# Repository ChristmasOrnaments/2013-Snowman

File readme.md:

This is the first in a series of Christmas ornaments I started making in 2013.

***

I had been experimenting with the Attiny series of MCUs and the Arduino environment, so I decided to make it a little more interesting than just a bare PCB. Flashing lights! I searched google and found a lot more info than I thought I would, but they were all designed to be plugged into a wall outlet. It was clear that this would be more fun if it were an actual Christmas ornament hanging from the tree, and I hate dragging wires around the tree (especially for a single ornament).  So battery powered it must be.

Unfortunately, the number of LEDs I wanted to use (~12) would come out to a current drain of 240mA. That’s a lot for any battery, but especially a small battery. AAA batteries would probably work, but the low-voltage Attinys required at least 1.8V (1.6V works usually, but the LEDs wouldn’t work at that voltage anyway). Using 2 AAA batteries would probably cause the branches of most Christmas trees to bend so much the ornament would just fall off. I tried a few buck/boost converters (like the MCP1640) to see if I could run the ornament from a single AAA cell, but most of these are only about 85% efficiency (the best I ever got was 60%). The input power of the converter was fairly substantial (5-10mA idle). In addition, the boost converter would be operating constantly, so even if the LEDs weren't flashing, the battery would still have a 5-10mA draw on it. That's enough to drain a 1000mAh AAA battery in 4 days! I'm sure if I had spent more time trying to optimize the boost converter I could have made it work. The MCP1640 has an enable pin, so I could have used the MCU to put the converter to sleep, if I could find a charge pump that would work to wake the MCU, and then the converter. Too complicated...

I found an interesting technique for controlling many LEDs from only a few MCU pins, called [Charlieplexing](https://en.wikipedia.org/wiki/Charlieplexing)…  It’s a really simple concept, so if you haven't heard of it I suggest you read the wiki page. I did a little more research and found [the UnaClocker's blog](https://web.archive.org/web/20131228142659/http://www.neonsquirt.com/xmas_ornament2012.html), and he had already done what I was doing! Well, sort of. It was still wall-powered, but since charlieplexing never lights more than a single LED at once, the MAXIMUM current draw will be the MCU (which is a few milliamps, maybe) plus the current draw of a single LED. So, ~10mA. This could easily run from a 3V CR2032 watch battery. Small, lightweight, and available at every drug store!

I prototyped a  small panel of 12 charlieplexed LEDs and it worked great. I was able to control 12 separate LEDs from an Attiny85 (8-pin) MCU. The more LEDs you turn on at once, the dimmer they get (since it is multiplexing the LEDs and turning them on and off individually, very quickly).

Eventually I designed the PCB with the snowman on it, and etched a board for testing. You'll notice the PCB has a little pushbutton on it.  It's nothing fancy, it just resets the MCU which gives you the ability to "play" the light show whenever you want (the first thing the MCU does is run through the LED patterns, before going to sleep). Doing it this way also saves a pin in case I want  to add more LEDs to a future version.

Here's the schematic and some pics of the demo board:

I found that using a long list of *digitalWrite* commands to display a pattern wasn’t going to be very space efficient (these things max out at 8k, and I’d rather use the 4k version). I found [this instructable](https://www.instructables.com/CharliePlexed-LED-string-for-the-Arduino/) which uses a byte-array to store the patterns in the form of a single string of binary data representing a single "frame" of the pattern to display. It's just an array holding 1's and 0's.  

Matching each LED with the corresponding element of the array can be tricky, so I came up with an excel spreadsheet to help build the strings of bytes for each frame in the pattern. I used the *CONCATENATE* function to simply string the contents of all the cells into a single line separated by commas, just like in the array. I set the cells up with colored backgrounds so it looked like the LEDs on the PCB.  I also added a button macro to clear the cells out, so it would be a little easier to make each frame (I didn’t have to go reset each cell to 0, the button reset them all to 0 instantly). If you don't want to use the macro, simply build a new document using CONCATENATE (or whatever your office program provides).

That gave me a bunch of different patterns I could go through when lighting the LEDs. I found a nice little [battery run-time calculator](http://oregonembedded.com/batterycalc.htm) online, which helped me guess how long the batteries would last. It turns out, even at 10mA the CR2032 battery wouldn't last very long if it was running constantly.  Instead, it uses the hardware watchdog timer to wake the MCU every 8 seconds. It then increments a counter variable and goes back to sleep (it only draws a few microamps when sleeping). Once the counter reaches a certain value (SleepTime), it executes the functions to display LED patterns. 

Read through the code comments for an explanation of how that works, but basically you set SleepTime to however many seconds you want it to wait before it turns on again (so, 300=5 minutes, etc). Since I'm using the internal clocks of the MCUs (which are known to be very inaccurate) I also adjusted the times a little bit. if you want a 5 minute wake time, then you need to use something around 300, but 300 will almost certainly NOT be 5 minutes.

My first prototype lasted from the beginning of October through the following January. It really depends on the voltages of your LEDs. I liked blue and green (TRUE green) LEDs, which tend to have a forward voltage of 3V. that means the CR2032 battery (which is a 3V battery) has to be pretty full to get the LEDs to light up brightly.  They usually go out first, around 2.4V. The red and yellow LEDs actually continued to work for at least another month before I ended the test (the MCUs will work down to about 1.6V, below that they become unstable). I thought 5 months was plenty of battery life for something that was intended to last through December. That being said, I would avoid using blue since it starts to dim much quicker than the others.

I had the PCBs manufactured by iTead Studio and assembled them:

Here's the ornament in action:

### Compiling

* Install [ATTinyCore](https://github.com/spencekonde/attinycore) using the boards manager
* Select **Attiny25/45/85 (No bootloader)** from the boards list
* Set the *Clock source* to **4MHz (internal)** (With newer versions, you may need to use 8MHz with a scalar variable to lower it to 4MHz)
* Set *B.O.D* to **Disabled**
* Select **Burn Bootloader** to write the changes
* Compile and write the program to the MCU

If using another method to program the MCU, just remember you need to set the fuses properly both for correct speed and for the power saving features. The fuses (for an ATTINY45) should be:

Low: C3  
High: DF  
Extended: FF

You can see the effect of different fuse settings (and their values) [here](http://www.engbedded.com/fusecalc/).

### Resources

**Charlieplexing Code using a byte array:**  
[https://www.instructables.com/CharliePlexed-LED-string-for-the-Arduino/](https://www.instructables.com/CharliePlexed-LED-string-for-the-Arduino/)

**Battery calculator:**  
[http://oregonembedded.com/batterycalc.htm](http://oregonembedded.com/batterycalc.htm)

**Power saving information:**  
[http://www.gammon.com.au/forum/?id=11497](http://www.gammon.com.au/forum/?id=11497)  
[http://www.insidegadgets.com/2011/02/05/reduce-attiny-power-consumption-by-sleeping-with-the-watchdog-timer](http://www.insidegadgets.com/2011/02/05/reduce-attiny-power-consumption-by-sleeping-with-the-watchdog-timer/)  
[http://www.nongnu.org/avr-libc/user-manual/group\_\_avr\_\_power.html](http://www.nongnu.org/avr-libc/user-manual/group__avr__power.html)

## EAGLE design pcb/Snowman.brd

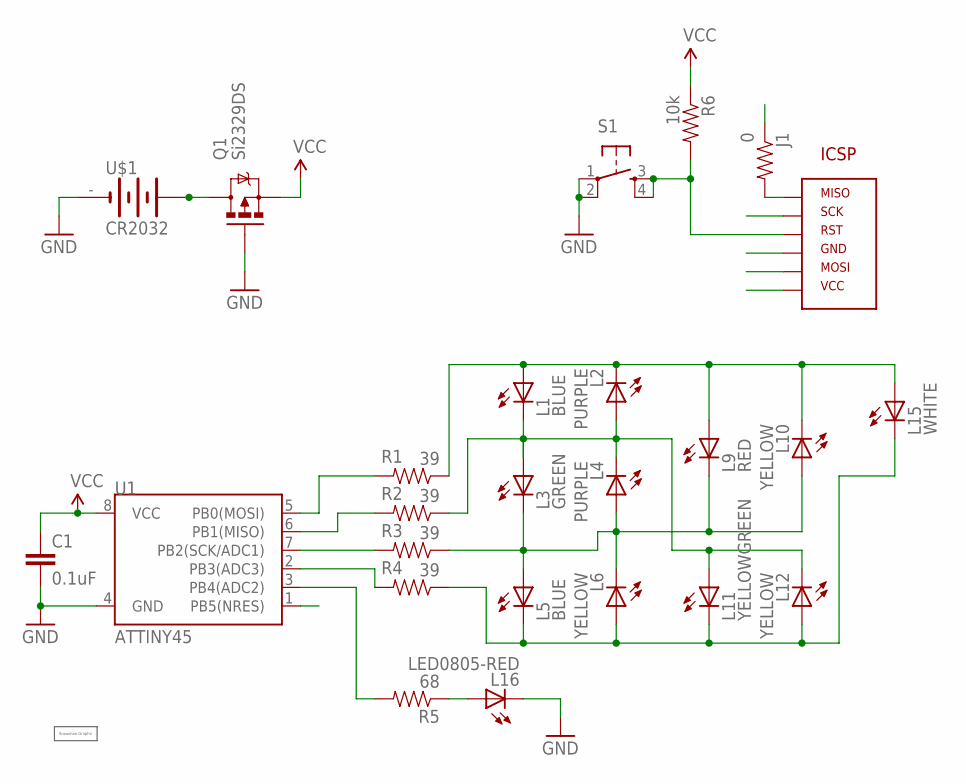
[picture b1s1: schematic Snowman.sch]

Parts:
C1: 0.1uF; 0805
J1: 0; 0805
L1, L5: BLUE; LED-0805-RED
L2, L4: PURPLE; LED-0805-GREEN
L3: GREEN; LED-0805-RED
L6, L10: YELLOW; LED-0805-GREEN
L9: RED; LED-0805-RED
L11: YELLOWGREEN; LED-0805-GREEN
L12: YELLOW; LED-0805-RED
L15: WHITE; LED-0805-RED
L16: LED0805-RED; LED-0805-RED
Q1: Si2329DS; SOT23-3
R1, R2, R3, R4: 39; 0805
R5: 68; 0805
R6: 10k; 0805
S1: TAC_SWITCHSMD; TACTILE_SWITCH_SMD
U1: ATTINY45; SO08-EIAJ
U$1: CR2032; BAT-HLD-001
U$2: 5X6_SNOWMAN5X5; 5X5_SNOWMAN
U$3: AVR_ICSP_6P6PIN; AVR_ICSP_6P_SMD

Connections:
GND: C1.2, L16.C, Q1.1 (G), S1.1, S1.2, U1.4 (GND), U$1.-, U$3.GND
L12: L1.C, L2.A, L3.A, L4.C, L11.A, L12.C, R2.1
MISO: J1.1, R2.2, U1.6 (PB1(MISO))
MOSI: R1.2, U1.5 (PB0(MOSI)), U$3.MOSI
unnamed: Q1.3 (D), U$1.+@1 (+), U$1.+@2 (+)
unnamed: R5.2, U1.3 (PB4(ADC2))
unnamed: L3.C, L4.A, L5.A, L6.C, L9.C, L10.A, R3.1
unnamed: R4.2, U1.2 (PB3(ADC3))
unnamed: L5.C, L6.A, L11.C, L12.A, L15.C, R4.1
unnamed: L1.A, L2.C, L9.A, L10.C, L15.A, R1.1
unnamed: L16.A, R5.1
unnamed: J1.2, U$3.MISO
RST: R6.2, S1.3, S1.4, U1.1 (PB5(NRES)), U$3.RST
SCK: R3.2, U1.7 (PB2(SCK/ADC1)), U$3.SCK
VCC: C1.1, Q1.2 (S), R6.1, U1.8 (VCC), U$3.VCC

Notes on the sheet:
ICSP

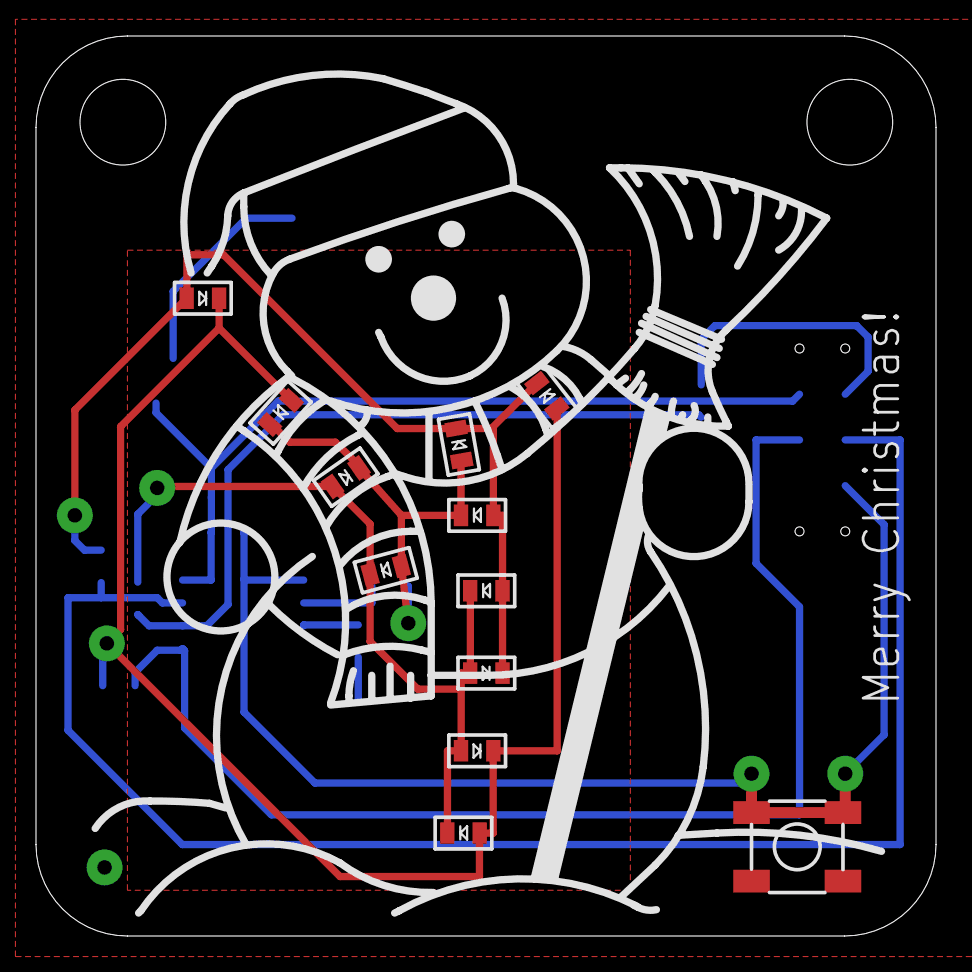
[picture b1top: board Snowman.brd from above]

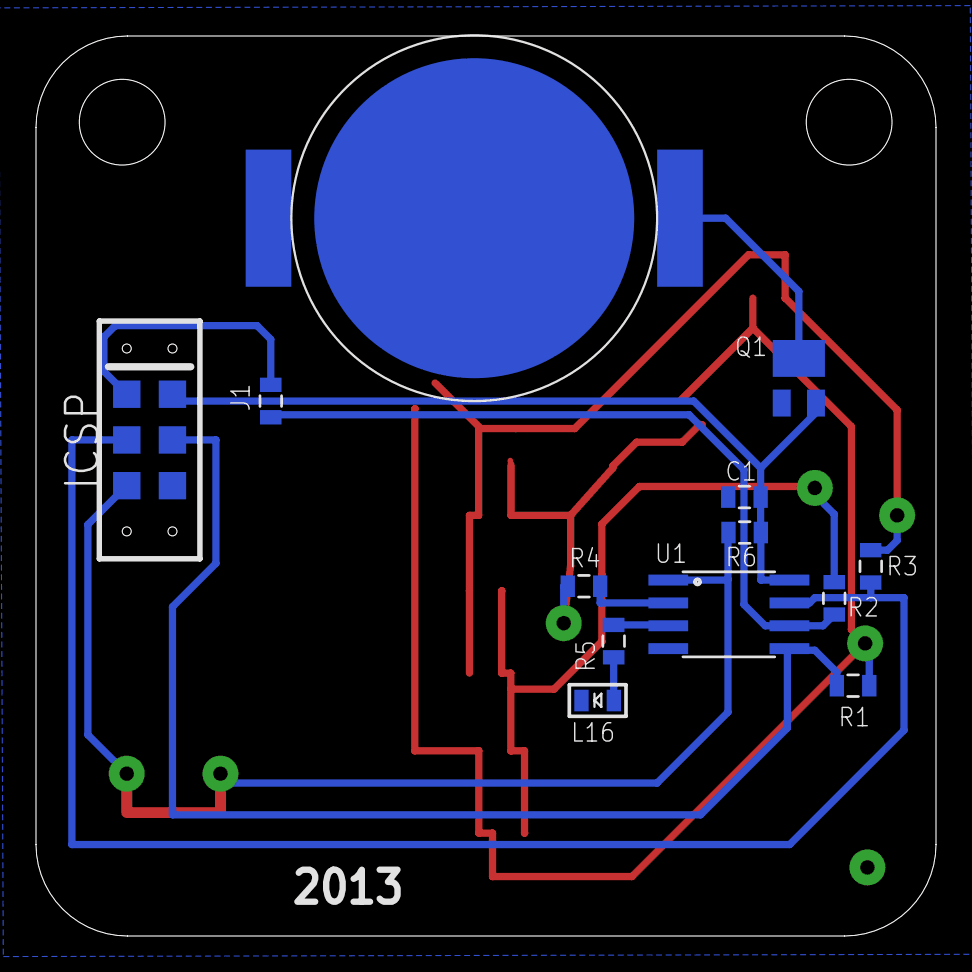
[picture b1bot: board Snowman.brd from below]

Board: 2 copper layers, 50.0 x 50.0 mm, 26 parts (13 on the bottom side), 15 nets.

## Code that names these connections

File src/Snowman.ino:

/*
 * ATTiny85_Internal_8MHz_Template.cpp
 *
 * Created: 6/28/2013 6:12:11 PM
 * Charlieplexing functions modeled after the code found here:
 *   http://www.instructables.com/id/CharliePlexed-LED-string-for-the-Arduino/step7/Coding-the-Arduino/
 */ 

#ifdef F_CPU  
#undef F_CPU
#endif  
#define F_CPU 4000000 // 4 MHz

// ATMEL ATTINYx5 / ARDUINO
//
//                            ____
//         (D5/A0) RST/PB5  1|*   |8  VCC
//   PWM   (D3/A3)     PB3  2|    |7  PB2  (D2/A1)
//   PWM   (D4/A2)     PB4  3|    |6  PB1  (D1)     PWM
//                     GND  4|____|5  PB0  (D0)     PWM

#include <avr/pgmspace.h>
// Power Mgt:
#include <avr/sleep.h>
#include <avr/wdt.h>

// FUNCTION PROTOTYPES
void displayChar(int from, int through, int tranSpeed); // loads a Pattern from above. From & through specify what patterns to show. tranSpeed is the speed of the frames
void turnon(int led); // This turns on a certian led from the list of leds
void alloff(); // This turns all the LED's off
void setup_watchdog(int ii);
void system_sleep();

// ******************************************************************************************************************
//
// Much of the charlieplex code has been modified from http://www.instructables.com/id/CharliePlexed-LED-string-for-the-Arduino/step7/Coding-the-Arduino/
// The power management code is from 

#define LEDCount 11
byte pins[4];
//const byte LEDCount = 20;

// The attiny85 watchdog only sleeps for 8 seconds at a time, so for a longer period of time we need to setup a counter variable
//   and check that against the # of times it wakes up.
// The internal clock isn't very accurate, so you need to factor that in. My tests show a deviation of ~0.9198 at 900 seconds,
//   so a rough equation would be [ SleepTime = DesiredTime * 0.9198 ]
// Every MCU will be different, so some experimentation will be necessary if you want accurate intervals
// Some example times:
//   5:00 -> 276
//  10:00 -> 552
//  15:00 -> 828
//  30:00 -> 1656
int SleepTime = 416; // Sleep time in seconds

int SleepCnt = SleepTime/8; // counter for watchdog wake timer

// blinkdelay is used by displayChar to set the microseconds the LED will be on, then off. It can affect brightness, but mostly affects speed
// blinkdelay could be replaced with a timeOn and timeOff to facilitate a type of PWM to increase LED brightness at low voltage 
//      (using a small Rs at higher voltage would be bad for LED unless turn-on time can be limited with this)
int blinkdelay = 50;   //Speed Param 1: smaller = faster
// runSpeed is the number of times displayChar will loop through each pattern before going to the next. Again, this affects speed
byte runSpeed = 50;      //Speed Param 2: smaller = faster (0-255) - this can be set individually when calling displayChar()

#ifndef cbi
#define cbi(sfr, bit) (_SFR_BYTE(sfr) &= ~_BV(bit))
#endif
#ifndef sbi
#define sbi(sfr, bit) (_SFR_BYTE(sfr) |= _BV(bit))
#endif
volatile boolean f_wdt = 1;

const byte LEDConnections[LEDCount][2] ={   // This stores which outputs the LEDs are connected to: { Anode, Cathode }
// Bottom Row
       { 0 , 1 },    //X1
       { 1 , 2 },    //X3
       { 2 , 3 },    //X5
       // Row 1
       { 1 , 0 },    //X2            
       { 2 , 1 },    //X4
       { 3 , 2 },    //X6
       // Row 2
       { 0 , 2 },    //X9
       { 1 , 3 },    //X11
       // Row 3
       { 2 , 0 },    //X10
       { 3 , 1 },    //X12
       // Row 4
       { 0 , 3 }    //X15
};

const byte displays[][LEDCount] PROGMEM ={  // This stores the array in Flash ROM.

// All Off (0)
	{0,0,0,0,0,0,0,0,0,0,0},

 // All LEDs Flash (1-2)
	{1,1,1,1,1,1,1,1,1,1,1},
	{0,0,0,0,0,0,0,0,0,0,0},

// Blink Hat (3-4)
        {0,0,0,0,0,0,0,0,1,0,0},
        {0,0,0,0,0,0,0,0,0,0,0},

// Blink Scarf (5-6)
	{0,0,0,0,0,1,1,1,0,1,1},
	{0,0,0,0,0,0,0,0,0,0,0},

// Blink Buttons (7-8)
	{1,1,1,1,1,0,0,0,0,0,0},
	{0,0,0,0,0,0,0,0,0,0,0},

// Run from hat to scarf to buttons and back to hat (9-30)
	{0,0,0,0,0,0,0,0,1,0,0},
	{0,0,0,0,0,0,1,0,0,0,0},
	{0,0,0,0,0,1,0,0,0,0,0},
	{0,0,0,0,0,0,0,0,0,0,1},
	{0,0,0,0,0,0,0,1,0,0,0},
	{0,0,0,0,0,0,0,0,0,1,0},
	{0,0,0,0,0,0,0,1,0,0,0},
	{0,0,0,0,0,0,0,0,0,0,1},
	{0,0,0,0,0,1,0,0,0,0,0},
	{0,0,1,0,0,0,0,0,0,0,0},
	{0,0,0,0,1,0,0,0,0,0,0},
	{0,1,0,0,0,0,0,0,0,0,0},
	{0,0,0,1,0,0,0,0,0,0,0},
	{1,0,0,0,0,0,0,0,0,0,0},
	{0,0,0,1,0,0,0,0,0,0,0},   // start going back up
	{0,1,0,0,0,0,0,0,0,0,0},
	{0,0,0,0,1,0,0,0,0,0,0},
	{0,0,1,0,0,0,0,0,0,0,0},
	{0,0,0,0,0,1,0,0,0,0,0},
	{0,0,0,0,0,0,1,0,0,0,0},
	{0,0,0,0,0,0,0,0,1,0,0},
	{0,0,0,0,0,0,0,0,0,0,0},

// Blink Hat, Scarf, Buttons (leaving each on) (31-34)
        {0,0,0,0,0,0,0,0,1,0,0},
	{0,0,0,0,0,1,1,1,1,1,1},
	{1,1,1,1,1,1,1,1,1,1,1},
	{0,0,0,0,0,0,0,0,0,0,0},

// All On (35)
	{1,1,1,1,1,1,1,1,1,1,1}
};

void setup()   {        
	// initialize the digital pin as an output:
	pins[0] = 0;
	pins[1] = 1;
	pins[2] = 2;
	pins[3] = 3;

	// Status LED
    pinMode(4, OUTPUT);

	setup_watchdog(9); // Watchdog timer; approximately 8 seconds sleep
}

void loop()                     
{
	if (f_wdt==1) {  // wait for timed out watchdog / flag is set when a watchdog timeout occurs

		f_wdt=0;       // reset flag
		if (SleepCnt >= (SleepTime/8)) {
			SleepCnt = 0; // Reset sleep counter
			
// Code to execute after we wake from sleep:

			// displayChar( from, through, tranSpeed )
			
			// Run through the whole thing  
			for (int loop=0; loop<2; loop++) {
				displayChar(9,30, 35); 
			}

			// Hat to scarf to buttons
			for (int loop=0; loop<3; loop++) {
				displayChar(31,34, runSpeed);
			}
			
			// Blink them all  
			for (int loop=0; loop<3; loop++) {
				displayChar(1,2, runSpeed); 
			}

// End of wake code

			//pinMode(0,INPUT); // Normally you would set the pinMode to INPUT to save power, but since the charlieplexing code does this, we don't need to here
			system_sleep();
			//pinMode(0,OUTPUT); // Set the pinmode back to OUTPUT, as it was before	
		} else {
			SleepCnt++;
			//pinMode(0,INPUT); // Normally you would set the pinMode to INPUT to save power, but since the charlieplexing code does this, we don't need to here
			system_sleep();
			//pinMode(0,OUTPUT); // Set the pinmode back to OUTPUT, as it was before
		}
  }	
}

// Charlieplexing Code
// *********************************************************************************************

// Courtesy of "copmutergeek"
// http://www.instructables.com/id/CharliePlexed-LED-string-for-the-Arduino/step7/Coding-the-Arduino/
void displayChar(int from, int through, int tranSpeed)// loads a Pattern from above. From & through specify what patterns to show. tranSpeed is the speed of the frames (smaller=faster)
{
  boolean run = true;
  byte k;
  int t = from;
  while(run == true)
  {
    for(int i = 0; i < tranSpeed; i++)
    {
      for(int j = 0; j < LEDCount; j++)
      {
        k = pgm_read_byte(&(displays[t][j]));
        if (k == 2)
        {
          run = false;
        }
        else if(k == 1)
        {
          turnon(j);
          delayMicroseconds(blinkdelay);
          alloff();
        }
        else if(k == 0)
        {
          delayMicroseconds(blinkdelay);
        }
      }
    }
    if(through == t){
      return;
    }
    t++;
  }
}

void turnon(int led) // This turns on a certian led from the list of leds
{
//  int pospin = LEDConnections[led][0] + 2;  //  <-- what is the +2 for?
//  int negpin = LEDConnections[led][1] + 2;
  int anode = LEDConnections[led][0];
  int cathode = LEDConnections[led][1];
  pinMode (anode, OUTPUT);
  digitalWrite (anode, HIGH);
  pinMode (cathode, OUTPUT);
  digitalWrite (cathode, LOW);
}

void alloff() // This turns all the LED's off
// TM - added sizeof(pins) to determine pin count (instead of hard-coded counts)
{
  for(int i = 0; i < sizeof(pins); i++)
  {
    pinMode (pins[i], INPUT);
  }
}

// Power Management
// *********************************************************************************************

// set system into the sleep state
// system wakes up when watchdog is timed out
void system_sleep() {
	cbi(ADCSRA,ADEN);                    // switch Analog to Digitalconverter OFF

	set_sleep_mode(SLEEP_MODE_PWR_DOWN); // sleep mode is set here
	sleep_enable();

	sleep_mode();                        // System sleeps here

	sleep_disable();                     // System continues execution here when watchdog timed out
	sbi(ADCSRA,ADEN);                    // switch Analog to Digitalconverter ON
}

// 0=16ms, 1=32ms,2=64ms,3=128ms,4=250ms,5=500ms
// 6=1 sec,7=2 sec, 8=4 sec, 9= 8sec
void setup_watchdog(int ii) {

	byte bb;
	int ww;
	if (ii > 9 ) ii=9;
	bb=ii & 7;
	if (ii > 7) bb|= (1<<5);
	bb|= (1<<WDCE);
	ww=bb;

	MCUSR &= ~(1<<WDRF);
	// start timed sequence
	WDTCR |= (1<<WDCE) | (1<<WDE);
	// set new watchdog timeout value
	WDTCR = bb;
	WDTCR |= _BV(WDIE);
}

// Watchdog Interrupt Service / is executed when watchdog timed out
ISR(WDT_vect) {
	f_wdt=1;  // set global flag
}

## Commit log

2026-03-22 initial
2026-03-22 replaced mp4 video with a gif
2026-03-22 fixed readme

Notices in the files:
parts and their libraries:
SparkFun: Licensing: CC v3.0 Share-Alike You are welcome to use this library for commercial purposes.
